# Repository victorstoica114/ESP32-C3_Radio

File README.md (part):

# ESP32-C3 Radio

PlatformIO project for testing multiple radio modules with an ESP32-C3 board,
an optional SSD1306 OLED display, and serial/AT-command based firmware variants.

The project is organized as a single PlatformIO application. The active radio
module and firmware variant are selected from `src/main.cpp`, and the matching
source file is included by `src/module_selection.h`.

## Measured radio energy

The repository includes a measured comparison of TX and RX event energy across
28 radio-module and board variants for a common 32-byte application payload.
The logarithmic scale makes the full range visible, from NRF24L01 devices to
high-power E32 and LoRa implementations. Click the chart to open the complete
35-page comparative study.

## Repository layout

| Folder | Purpose |
| --- | --- |
| `src/` | ESP32 firmware |
| `PCB/` | KiCad boards and supply-voltage table |
| `measurements/raw/` | All local PPK captures and source metadata; excluded from Git |
| `power_profiler/radio_power_profiler/`, `power_profiler/tools/` | Acquisition UI and analysis tools |
| `power_profiler/comparisons/` | Reviewed results and comparison exports |
| `power_profiler/audits/` | Measurement checks and supporting evidence |
| `power_profiler/study/` | Comparative study, figures and editable sources |
| `test/`, `power_profiler/tests/` | Radio checks and software tests |

See [the measurement directory guide](measurements/README.md) for RAW and WIRE
locations. New captures use the same local directory regardless of the shell's
working directory.

See `CHANGELOG.md` for notable project changes.

## License

Project source code is released under the MIT License. See `LICENSE`.

Third-party libraries and vendor/manufacturer datasheets keep their own
licenses and redistribution terms. See `THIRD_PARTY_NOTICES.md`.

## Hardware target

- MCU: ESP32-C3 DevKitC-02
- Framework: Arduino
- Build system: PlatformIO
- Optional display: SSD1306 128x64 OLED via U8g2

See the [module supply-voltage list](PCB/TENSIUNI_ALIMENTARE.md) for the
3.3 V and 5 V inputs used by the different radio adapter boards.

Common pins used by many sketches:

- OLED SDA: GPIO 5
- OLED SCL: GPIO 6
- Status LED: GPIO 8
- SPI CS/NSS: GPIO 7

The integrated OLED on the ESP32-C3 OLED devboard is wired to GPIO 5/GPIO 6.
Module schematics may expose other SDA/SCL labels for external headers, but that
does not change the onboard OLED wiring. If a future board/module variant uses a
different OLED wiring, document that exception in the module section below.

Some radio modules share GPIO 5/GPIO 6 with SPI MISO/MOSI. In the affected
firmware variants, the OLED I2C bus is released after the splash screen and the
SPI bus is reinitialized before starting the radio.

## Dependencies

Defined in `platformio.ini`:

- `jgromes/RadioLib`
- `olikraus/U8g2`
- `xreef/LoRa_E32_Series_Library`
- Arduino ESP32 built-in libraries such as `SPI`, `Wire`, and `EEPROM`

## Selecting firmware

Edit `src/main.cpp`:

```cpp
#define RADIO_MODULE  RADIO_EBYTE_E79_CC1352P
#define RADIO_PROGRAM BRIDGE
```

Keep this include after the two defines:

```cpp
#include "module_selection.h"
```

## Supported modules

Use these values for `RADIO_MODULE` in the ESP32 PlatformIO firmware:

| RADIO_MODULE | Folder | Radio/module |
| --- | --- | --- |
| `RADIO_CC1101_V1_433` | `src/CC1101` | CC1101 V1, 433 MHz hardware/front-end |
| `RADIO_CC1101_V2_868` | `src/CC1101` | CC1101 V2, 868 MHz hardware/front-end |
| `RADIO_HC12` | `src/HC-12` | HC-12 UART radio |
| `RADIO_NRF24L01` | `src/NRF24L01` | nRF24L01/nRF24L01+ |
| `RADIO_RA01_SX1278` | `src/RA-01(SX1278)` | Ai-Thinker RA-01, SX1278 |
| `RADIO_RA01H_SX1276` | `src/RA-01H(SX1276)` | RA-01H, SX1276 |
| `RADIO_RA01SH_SX1262` | `src/RA-01SH(SX1262)` | RA-01SH, SX1262 |
| `RADIO_RA02_SX1278` | `src/RA-02(SX1278)` | RA-02, SX1278 |
| `RADIO_E28_SX1280` | `src/E28(SX1280)` | E28, SX1280 2.4 GHz |
| `RADIO_EBYTE` | `src/Ebyte` | Ebyte E32 UART LoRa module |
| `RADIO_EBYTE_E32_868T30D` | `src/Ebyte` | Ebyte E32 868T30D UART LoRa module |
| `RADIO_EBYTE_E32_433T33D` | `src/Ebyte` | Ebyte E32 433T33D UART LoRa module |
| `RADIO_EBYTE_E22_SX1268` | `src/Ebyte E22(SX1268)` | Ebyte E22 SPI LoRa module, SX1268 |
| `RADIO_EBYTE_E280_SX1280` | `src/Ebyte E280(SX1280)` | Ebyte E280-2G4T12S UART/TTL module, SX1280 |
| `RADIO_EBYTE_E79_CC1352P` | `src/Ebyte E79(CC1352P)` | Ebyte E79-400DM2005S, TI CC1352P wireless MCU |
| `RADIO_EBYTE_E07_400M10S` | `src/CC1101` | Ebyte E07-400M10S, CC1101, 410-450 MHz, 10 dBm nominal |
| `RADIO_EBYTE_E07_400MM10S` | `src/CC1101` | Ebyte E07-400MM10S, CC1101, 10 dBm nominal |
| `RADIO_EBYTE_E07_900MM10S` | `src/CC1101` | Ebyte E07-900MM10S, CC1101, 855-925 MHz, 10 dBm nominal |
| `RADIO_EBYTE_E07_433M20S` | `src/CC1101` | Ebyte E07-433M20S, CC1101 + PA/LNA, 425-450.5 MHz, 20 dBm nominal |
| `RADIO_XL1276_D01_SX1276` | `src/XL1276-D01 (SX1276)` | XL1276-D01, SX1276 |

Standalone module-side radio firmware:

| Firmware | Primary repository | Local reference | Radio/module | Status |
| --- | --- | --- | --- | --- |
| RA08 AT modem | [victorstoica114/RA-08_AT-Commands](https://github.com/victorstoica114/RA-08_AT-Commands) | `src/RA-08(ASR6601)` | Ai-Thinker RA-08, ASR6601 LPWAN SoC | Functional and tested with two modules |
| RA09 AT modem | [victorstoica114/RA-09_AT-Commands](https://github.com/victorstoica114/RA-09_AT-Commands) | `src/RA-09(STM32WLE5)` | Ai-Thinker RA-09, STM32WLE5CCU6 Sub-GHz wireless MCU | Functional and tested with two modules; 20/20 bidirectional frames |
| E79 AT modem | [victorstoica114/Ebyte-E79-CC1352P-_AT_Modem_Firmware](https://github.com/victorstoica114/Ebyte-E79-CC1352P-_AT_Modem_Firmware) | `src/Ebyte E79(CC1352P)/CC1352P_AT_Modem_Firmware` | Ebyte E79-400DM2005S, TI CC1352P wireless MCU | Firmware 0.3.0; seven RF profiles; 343/0 hardware tests |

## Radio module gallery

The photographs below show the carrier boards and physical module
implementations used by this project and its power-measurement campaigns.

<table>
  <tr>
    <td align="center"><br><strong>CC1101 V1</strong></td>
    <td align="center"><br><strong>CC1101 V2</strong></td>
    <td align="center"><br><strong>E07-400M10S</strong></td>
    <td align="center"><br><strong>E07-433M20S</strong></td>
  </tr>
  <tr>
    <td align="center"><br><strong>E07-900MM10S</strong></td>
    <td align="center"><br><strong>E22</strong></td>
    <td align="center"><br><strong>E28</strong></td>
    <td align="center"><br><strong>E280</strong></td>
  </tr>
  <tr>
    <td align="center"><br><strong>E32-433T20D</strong></td>
    <td align="center"><br><strong>E32-433T33D</strong></td>
    <td align="center"><br><strong>E32-868T20D</strong></td>
    <td align="center"><br><strong>E32-868T30D</strong></td>
  </tr>
  <tr>
    <td align="center"><br><strong>E79 ESP32 bridge</strong></td>
    <td align="center"><br><strong>E79 direct UART</strong></td>
    <td align="center"><br><strong>HC-12</strong></td>
    <td align="center"><br><strong>nRF24L01</strong></td>
  </tr>
  <tr>
    <td align="center"><br><strong>nRF24L01 PA/LNA</strong></td>
    <td align="center"><br><strong>RA-01H</strong></td>
    <td align="center"><br><strong>RA-01SH</strong></td>
    <td align="center"><br><strong>RA-02</strong></td>
  </tr>
  <tr>
    <td align="center"><br><strong>RA-02 capacitor variant</strong></td>
    <td align="center"><br><strong>RA-08</strong></td>
    <td align="center"><br><strong>RA-09</strong></td>
    <td align="center"><br><strong>XL1276-D01</strong></td>
  </tr>
  <tr>
    <td align="center"><br><strong>SX1278 naked</strong></td>
    <td align="center"><br><strong>SX1278 shielded</strong></td>
    <td align="center"><br><strong>SX1278 capacitor</strong></td>
    <td align="center"><br><strong>SX1278 level shifter</strong></td>
  </tr>
</table>

## Firmware variants

Use these values for `RADIO_PROGRAM`:

| RADIO_PROGRAM | Meaning |
| --- | --- |
| `AT_COMMANDS` | AT-command shell and, for most modules, transparent TX mode |
| `BIDIRECTIONAL_RX_TX` | Bidirectional RX/TX example |
| `RECEIVE` | Receive-only example |
| `SETTINGS` | Radio settings/configuration example |
| `TRANSMIT` | Transmit-only example |
| `BRIDGE` | UART/Serial bridge example |

Availability by module:

| Module | AT_COMMANDS | BIDIRECTIONAL_RX_TX | RECEIVE | SETTINGS | TRANSMIT | BRIDGE |
| --- | --- | --- | --- | --- | --- | --- |
| `RADIO_CC1101_V1_433` | yes | yes | yes | yes | yes | no |
| `RADIO_CC1101_V2_868` | yes | no | no | no | no | no |
| `RADIO_HC12` | yes | yes | no | no | no | no |
| `RADIO_NRF24L01` | yes | yes | no | no | no | no |
| `RADIO_RA01_SX1278` | yes | yes | no | yes | no | no |
| `RADIO_RA01H_SX1276` | yes | yes | no | no | no | no |
| `RADIO_RA01SH_SX1262` | yes | yes | no | yes | no | no |
| `RADIO_RA02_SX1278` | yes | yes | no | yes | no | no |
| `RADIO_E28_SX1280` | yes | yes | no | yes | no | no |
| `RADIO_EBYTE` | yes | no | no | no | no | yes |
| `RADIO_EBYTE_E32_868T30D` | yes | no | no | no | no | no |
| `RADIO_EBYTE_E32_433T33D` | yes | no | no | no | no | no |
| `RADIO_EBYTE_E22_SX1268` | yes | no | no | no | no | no |
| `RADIO_EBYTE_E280_SX1280` | yes | no | no | no | no | no |
| `RADIO_EBYTE_E79_CC1352P` | yes | no | no | no | no | yes |
| `RADIO_EBYTE_E07_400M10S` | yes | no | no | no | no | no |
| `RADIO_EBYTE_E07_400MM10S` | yes | no | no | no | no | no |
| `RADIO_EBYTE_E07_900MM10S` | yes | no | no | no | no | no |
| `RADIO_EBYTE_E07_433M20S` | yes | no | no | no | no | no |
| `RADIO_XL1276_D01_SX1276` | yes | no | yes | yes | yes | no |
| RA08 AT modem | yes | no | no | no | no | no |
| RA09 AT modem | yes | no | no | no | no | no |

If a module/program combination is not available, compilation stops with a clear
`#error` message from `src/module_selection.h`.

## External Module Firmware

Some modules are wireless MCUs rather than direct ESP32 radio peripherals. Their
module-side firmware is kept separately from the ESP32 PlatformIO firmware.

### Ai-Thinker RA-08

The RA-08 ASR6601 AT modem firmware lives in its own repository:
[victorstoica114/RA-08_AT-Commands](https://github.com/victorstoica114/RA-08_AT-Commands).
That project turns the RA-08 into a standalone UART AT radio modem. This
repository keeps only a small source reference under
`src/RA-08(ASR6601)` (`main.c`, `at_modem.c`, IRQ glue, and headers).
Build support, drivers, startup code, linker scripts, and the ARM GCC toolchain
belong in the separate RA-08 firmware repository.

The RA-08 modem was validated on two modules over USB serial at `115200` baud,
including AT command parsing, parameter validation, sleep/wake guardrails,
manual frequency mode, channel mode, and bidirectional packet exchange.

### Ai-Thinker RA-09

The RA-09 STM32WLE5CCU6 AT modem firmware lives in its own repository:
[victorstoica114/RA-09_AT-Commands](https://github.com/victorstoica114/RA-09_AT-Commands).
The application uses LPUART1 on PA2/PA3, exposed by the module as
`TX2`/`RX2`, and receives continuously after boot. Plain UART messages are
transmitted transparently, so `AT+SEND` is optional.

This repository keeps the modem application, LPUART1 setup, interrupt glue,
and RA-09 RF interface as a compact source reference under
`src/RA-09(STM32WLE5)`. The complete STM32 HAL, CMSIS, radio middleware,
startup code, linker script, CMake build, and flashing tools remain in the
dedicated firmware repository.

The validated image was programmed through the STM32 UART bootloader on two
carriers, one using CH340C and one using CH9340C. Both passed modem identity
and configuration checks, followed by 10 of 10 transparent-data frames in
each direction without corruption.

## Build

From the project root:

```sh
pio run
```

Upload:

```sh
pio run --target upload
```

Open serial monitor:

```sh
pio device monitor
```

The serial baud rate depends on the selected firmware. Many AT-command variants
use `9600`, while some bridge examples use `115200`.

## AT command reference

All AT-command firmware variants implement `AT` for a basic connectivity check
and `AT?`/`AT+HELP` for the firmware-local help text. Commands not implemented
by the selected module return `#ERROR`.

Error responses are intentionally easy to filter: they start with `#` and are
printed with a CRLF line ending. Generic failures return `#ERROR`; specific
runtime guardrails return messages such as `#ERROR: RADIO_SLEEPING (send
AT+WAKE)`, `#ERROR: BRIDGE_OFF (send AT+BRIDGE=ON)`, or `#ERROR:
RADIO_NOT_READY (set config and run AT+APPLY)`.

`AT+DEFAULT` is intentionally kept as the safety net command. It restores known
firmware defaults, saves them where EEPROM/module storage is used, and reapplies
the radio configuration so communication can be recovered after a bad setting.

`AT+RX=OFF` means standby/receive disabled. Low-power sleep is a separate state
entered with `AT+SLEEP` and left with `AT+WAKE` where supported.

For UART radio modules, changing the module baud also retunes the ESP32 hardware
UART connected to that module. The ESP32 USB CDC serial port exposed to the PC is
virtual and is not used as the radio-module baud reference.

### CC1101

The Ebyte E07-400M10S, E07-400MM10S, E07-900MM10S, and E07-433M20S variants
use the same CC1101 AT firmware. Select the exact module with `RADIO_MODULE` so
the splash, configuration printout, allowed RF range, and EEPROM namespace
match the hardware. The E07-400M10S selection defaults to `433.920 MHz` and
limits `AT+FREQ` to its `410-450 MHz` RF range. The E07-900MM10S selection
defaults to `915.000 MHz` and limits `AT+FREQ` to its `855-925 MHz` RF range.
The E07-433M20S selection defaults to `433.920 MHz` and limits `AT+FREQ` to
its `425-450.5 MHz` RF range. On the local carriers, `GD00` is connected to
ESP32-C3 `GPIO1`, `GD02` to `GPIO3`, and module power passes through the
current-measurement jumper.

The local E07-900MM10S pair was hardware-validated at `915.000 MHz` using GFSK,
a 64-bit preamble, one tolerated sync-word bit error, CRC, and `-30 dBm`.
Those values are the firmware defaults and passed 20/20 isolated packets in
both directions. The modules support up to `10 dBm`, but the closely spaced
bench setup showed packet loss at higher power, consistent with receiver
overload; use more separation or RF attenuation for high-power tests.

The local E07-400M10S pair was hardware-validated at `433.920 MHz` with the
same conservative GFSK packet profile and `-30 dBm` TX power. Plain bridge
messages, without `AT+SEND`, passed 20/20 packets in both directions.

The local E07-433M20S pair was hardware-validated at `433.920 MHz`, GFSK, a
64-bit preamble, CRC, and the conservative `-30 dBm` CC1101 drive setting.
Automatic PA/LNA direction control and plain bridge traffic passed 20/20
packets in both directions.

Use `RADIO_CC1101_V1_433` for the local V1 CC1101 boards. Its firmware default
is `433.920 MHz`, the tested stable center frequency for the local 433 MHz
pair. Use `RADIO_CC1101_V2_868` for the local V2 CC1101 boards; that selection
uses the same firmware source, but `AT+DEFAULT` restores `868.000 MHz` and it
uses a separate EEPROM namespace. CC1101 chips can tune across multiple sub-GHz
bands, but the RF matching network, antenna, and any external PA/LNA are
band-specific. In the local test set, the V2 pair on COM39/COM40 was unreliable
at 433.920 MHz but passed cleanly at 868/869 MHz.

The E07-400MM10S selection compiles but still awaits equivalent paired-radio
hardware validation.

`E07-433M20S` includes an external PA/LNA and is rated around 20 dBm at module
level. Its active-HIGH `TXEN` and `RXEN` inputs are connected to ESP32-C3
`GPIO21` and `GPIO20`; the firmware switches them automatically and prevents
overlap. `AT+PWR` still controls the CC1101 drive/PATABLE preset exposed by
RadioLib, not a separate PA gain setting.

| Command | Meaning |
| --- | --- |
| `AT`, `AT?`, `AT+HELP`, `AT+CFG?` | Connectivity, help, and full configuration/status printout |
| `AT+APPLY`, `AT+RESET`, `AT+DEFAULT` | Apply current config, reset/reapply, or restore safe defaults |
| `AT+DEBUG=ON\|OFF`, `AT+DEBUG?` | Control debug output |
| `AT+BRIDGE=ON\|OFF`, `AT+BRIDGE?` | Control transparent serial-to-radio bridge mode |
| `AT+RX=ON`, `AT+RX=OFF` | Start receive or stop receive into standby |
| `AT+SLEEP`, `AT+WAKE` | Enter low-power sleep or wake and restore RX state |
| `AT+RSSI?`, `AT+LQI?`, `AT+STATUS?`, `AT+RANDOM?` | Packet/link diagnostics and one RSSI-noise random byte |
| `AT+FREQ?`, `AT+FREQ=<MHz>` | Query/set carrier frequency |
| `AT+BR?`, `AT+BR=<kbps>`, `AT+BR1..11` | Query/set bit rate or use a preset |
| `AT+DEV?`, `AT+DEV=<kHz>` | Query/set frequency deviation |
| `AT+BW?`, `AT+BW=<kHz>`, `AT+BW1..16` | Query/set receive bandwidth or use a preset |
| `AT+PWR?`, `AT+PWR=<-30\|-20\|-15\|-10\|0\|5\|7\|10>`, `AT+PWR1..8` | Query/set CC1101 drive power or use a preset |
| `AT+PRE?`, `AT+PRE=<bits>` | Query/set preamble length |
| `AT+SYNC?`, `AT+SYNC=<hex>` | Query/set 2-byte sync word |
| `AT+SYNCERR?`, `AT+SYNCERR=0\|1` | Query/set allowed sync-word error bits |
| `AT+CRC?`, `AT+CRC=ON\|OFF` | Query/set CRC |
| `AT+MOD?`, `AT+MOD=2FSK\|GFSK\|OOK\|4FSK` | Query/set modulation |
| `AT+SHAPE?`, `AT+SHAPE=NONE\|0.5` | Query/set data shaping |
| `AT+ENC?`, `AT+ENC=NRZ\|MANCHESTER\|WHITENING` | Query/set encoding |
| `AT+PKT?`, `AT+PKT=VARIABLE,<1..64>`, `AT+PKT=FIXED,<1..64>` | Query/set packet length mode |
| `AT+ADDR?`, `AT+ADDR=OFF`, `AT+ADDR=<node>,<broadcasts>` | Query/set address filtering |
| `AT+PROMISC?`, `AT+PROMISC=ON\|OFF` | Query/set promiscuous mode |
| `AT+CS?`, `AT+CS=ON\|OFF` | Query/set carrier-sense requirement |
| `AT+SETRADIO=FREQ,BR,DEV,BW,PWR,PRE,SYNC,CRC` | One-shot legacy CC1101 setup |

### HC-12

| Command | Meaning |
| --- | --- |
| `AT`, `AT?`, `AT+HELP`, `AT+CFG?` | Connectivity, help, and current firmware config |
| `AT+APPLY`, `AT+RESET`, `AT+DEFAULT` | Apply current config, reset/reapply, or restore defaults |
| `AT+DEBUG`, `AT+DEBUG=ON\|OFF`, `AT+DEBUG?` | Toggle/query debug output |
| `AT+BRIDGE=ON\|OFF`, `AT+BRIDGE?` | Control transparent USB Serial to HC-12 bridge |
| `AT+BAUD?`, `AT+BAUD=<1200..115200>` | Query/set HC-12 UART baud |
| `AT+UART?`, `AT+UART=8N1\|8O1\|8E1` | Query/set UART serial format |
| `AT+CHAN?`, `AT+CHAN=<0..127>` | Query/set HC-12 channel |
| `AT+POWER?`, `AT+POWER=<1..8>` | Query/set TX power level |
| `AT+FU?`, `AT+FU=<1..4>` | Query/set FU mode |
| `AT+V`, `AT+VERSION?` | Query module firmware version |
| `AT+INFO?` | Read module-side status/configuration |
| `AT+RAW=<cmd>` | Send a raw HC-12 AT command |
| `AT+SLEEP`, `AT+WAKE` | Put module to sleep or wake it |

### nRF24L01

| Command | Meaning |
| --- | --- |
| `AT`, `AT?`, `AT+HELP`, `AT+CFG?` | Connectivity, help, and full configuration/status printout |
| `AT+APPLY`, `AT+RESET`, `AT+DEFAULT` | Apply current config, reinitialize, or restore safe defaults |
| `AT+DEBUG=ON\|OFF`, `AT+DEBUG?` | Control debug output |
| `AT+STATUS?` | Print local RF/status information |
| `AT+RX=ON`, `AT+RX=OFF` | Start RX or enter standby |
| `AT+SLEEP`, `AT+WAKE` | Enter power-down or wake and restore RX state |
| `AT+FREQ?`, `AT+FREQ=<MHz>` | Query/set RF frequency |
| `AT+CHAN?`, `AT+CHAN=<0..125>` | Query/set 2.4 GHz channel |
| `AT+RATE?`, `AT+RATE=250\|1000\|2000` | Query/set data rate in kbps |
| `AT+PWR?`, `AT+PWR=<dBm>` | Query/set TX power |
| `AT+ADDR?`, `AT+ADDR=<hex>` | Query/set shared TX/RX pipe 0 address |
| `AT+ADDRWIDTH?`, `AT+ADDRWIDTH=3\|4\|5` | Query/set address width |
| `AT+TXADDR?`, `AT+TXADDR=<hex>` | Query/set TX address |
| `AT+RXADDR<n>?`, `AT+RXADDR<n>=<hex>` | Query/set RX pipe address, pipe `0..5` |
| `AT+PIPE<n>?`, `AT+PIPE<n>=ON\|OFF`, `AT+PIPES?` | Query/set pipe enable state |
| `AT+CRC?`, `AT+CRC=ON\|OFF` | Query/set CRC |
| `AT+AUTOACK?`, `AT+AUTOACK=<hexmask>` | Query/set auto-ack mask |
| `AT+AUTOACK<n>?`, `AT+AUTOACK<n>=ON\|OFF` | Query/set auto-ack for pipe `0..5` |
| `AT+RETRIES?`, `AT+RETRIES=<delay>,<count>` | Query/set retry delay/count |
| `AT+LNA?`, `AT+LNA=ON\|OFF` | Query/set LNA gain |
| `AT+DYN?`, `AT+DYN=ON\|OFF` | Query/set dynamic payloads |
| `AT+ACKPAY?`, `AT+ACKPAY=ON\|OFF` | Query/set ACK payload feature |
| `AT+PLEN?`, `AT+PLEN=<1..32>` | Query/set fixed payload length |

For transparent text payloads, nRF24L01 defaults to `AT+DYN=ON` so each serial
line can be sent at its actual length. If `AT+DYN=OFF` is selected, payload
lines must have exactly the configured `AT+PLEN` length; otherwise the firmware
returns `#ERROR: FIXED_PAYLOAD_LENGTH_MISMATCH`.

For sustained bidirectional validation across channel, rate, and power, use
`test/Test-Nrf24SustainedLink.ps1`. It records offered/received unique frames
and transmitter serial errors in a CSV plus a complete session log. The local
COM41/COM42 campaign is documented in
`power_profiler/comparisons/nrf24l01/VALIDATION.md`; it exposed repeatable
high-power loss at 250 and 1000 kbps, so the nRF24L01 web quick check includes
maximum-power/minimum-rate cases in both directions. The external-PA/LNA pair
on COM43/COM44 is characterized separately under
`power_profiler/comparisons/nrf24l01_pa/VALIDATION.md`; it must not be merged
with the plain-module baseline.

### SX1276/SX1278 modules

Applies to `RADIO_RA01_SX1278`, `RADIO_RA02_SX1278`,
`RADIO_RA01H_SX1276`, and `RADIO_XL1276_D01_SX1276`.

| Command | Meaning |
| --- | --- |
| `AT`, `AT?`, `AT+HELP`, `AT+CFG?` | Connectivity, help, and current config/status |
| `AT+APPLY`, `AT+RESET`, `AT+DEFAULT` | Apply current config, hardware reset/reapply, or restore defaults |
| `AT+DEBUG`, `AT+DEBUG=ON\|OFF`, `AT+DEBUG?` | Toggle/query debug output |
| `AT+RX=ON`, `AT+RX=OFF` | Start RX or stop RX into standby |
| `AT+SLEEP`, `AT+WAKE` | Enter sleep or wake and restore RX state |
| `AT+RSSI?`, `AT+SNR?`, `AT+FERR?`, `AT+CAD?`, `AT+RANDOM?` | Packet diagnostics, channel activity detection, random byte |
| `AT+FREQ?`, `AT+FREQ=<MHz>` | Query/set frequency; SX1278: `137..175` or `395..525`, SX1276: those bands plus `862..1020` |
| `AT+BW?`, `AT+BW=<kHz>` | Query/set LoRa bandwidth: `7.8`, `10.4`, `15.6`, `20.8`, `31.25`, `41.7`, `62.5`, `125`, `250`, `500` |
| `AT+SF?`, `AT+SF=<value>` | Query/set spreading factor |
| `AT+CR?`, `AT+CR=<5..8>` | Query/set coding rate denominator |
| `AT+SYNC?`, `AT+SYNC=<hex>` | Query/set sync word |
| `AT+PWR?`, `AT+PWR=<-4..17\|20>` | Query/set TX power |
| `AT+CURR?`, `AT+CURR=<0\|45..240>` | Query/set current limit where supported |
| `AT+PREAMBLE?`, `AT+PREAMBLE=<6..65535>` | Query/set preamble length |
| `AT+GAIN?`, `AT+GAIN=<0..6>` | Query/set RX gain where supported |
| `AT+CRC?`, `AT+CRC=ON\|OFF` | Query/set CRC |
| `AT+HEADER?`, `AT+HEADER=EXPLICIT`, `AT+HEADER=IMPLICIT,<1..255>` | Query/set explicit or implicit header mode |
| `AT+IQ?`, `AT+IQ=ON\|OFF` | Query/set IQ inversion |
| `AT+FHSS?`, `AT+FHSS=<0..255>` | Query/set FHSS hopping period |
| `AT+SET=<FREQ>,<BW>,<SF>,<CR>,<SYNC>,<PWR>,<CURR>,<PRE>,<GAIN>,<CRC>` | Batch-set LoRa parameters; some SX127x variants use the shorter format without `CURR`/`GAIN` |

### SX1262 RA-01SH

| Command | Meaning |
| --- | --- |
| `AT`, `AT?`, `AT+HELP`, `AT+CFG?` | Connectivity, help, and current config/status |
| `AT+APPLY`, `AT+RESET`, `AT+DEFAULT` | Apply current config, hardware reset/reapply, or restore defaults |
| `AT+DEBUG`, `AT+DEBUG=ON\|OFF`, `AT+DEBUG?` | Toggle/query debug output |
| `AT+RX=ON`, `AT+RX=OFF` | Start RX or stop RX into standby |
| `AT+SLEEP`, `AT+WAKE` | Enter sleep or wake and restore RX state |
| `AT+RSSI?`, `AT+SNR?`, `AT+FERR?`, `AT+CAD?`, `AT+RANDOM?`, `AT+STATUS?` | Packet/status diagnostics |
| `AT+FREQ?`, `AT+FREQ=<803..930 MHz>` | Query/set the RA-01SH front-end frequency |
| `AT+BW?`, `AT+BW=<kHz>` | Query/set bandwidth: `7.8`, `10.4`, `15.6`, `20.8`, `31.25`, `41.7`, `62.5`, `125`, `250`, `500` |
| `AT+SF?`, `AT+SF=<value>` | Query/set spreading factor |
| `AT+CR?`, `AT+CR=<5..8>` | Query/set coding rate denominator |
| `AT+SYNC?`, `AT+SYNC=<hex>` | Query/set sync word |
| `AT+PWR?`, `AT+PWR=<-9..22>` | Query/set TX power |
| `AT+CURR?`, `AT+CURR=<0..140>` | Query/set current limit |
| `AT+PREAMBLE?`, `AT+PREAMBLE=<1..65535>` | Query/set preamble length |
| `AT+GAIN?`, `AT+GAIN=<0..6>` | Query/set RX gain |
| `AT+CRC?`, `AT+CRC=ON\|OFF` | Query/set CRC |
| `AT+TCXO?`, `AT+TCXO=<0\|1.6..3.3>` | Query/set TCXO voltage, `0` for XTAL |
| `AT+REG?`, `AT+REG=LDO\|DCDC` | Query/set regulator mode |
| `AT+DIO2?`, `AT+DIO2=ON\|OFF` | Query/set DIO2 RF switch control |
| `AT+RXBOOST?`, `AT+RXBOOST=ON\|OFF` | Query/set boosted RX gain mode |
| `AT+HEADER?`, `AT+HEADER=EXPLICIT`, `AT+HEADER=IMPLICIT,<1..255>` | Query/set header mode |
| `AT+IQ?`, `AT+IQ=ON\|OFF` | Query/set IQ inversion |
| `AT+LDRO?`, `AT+LDRO=ON\|OFF` | Force low-data-rate optimization (`ON`) or restore automatic selection (`OFF`) |
| `AT+SET=<FREQ>,<BW>,<SF>,<CR>,<SYNC>,<PWR>,<CURR>,<PRE>,<GAIN>,<CRC>` | Batch-set LoRa parameters |

### SX1268 Ebyte E22

This is the SPI E22 variant wired as `NSS=GPIO7`, `DIO1=GPIO1`,
`BUSY=GPIO3`, `RESET=GPIO10`, with SPI on `GPIO4/5/6`. The onboard OLED uses
the same devboard wiring as the SX1278 tests: `SDA=GPIO5`, `SCL=GPIO6`. Because
those pins are shared with SPI, the firmware initializes the radio, recovers the
OLED I2C bus, draws the OLED splash, releases I2C, then reinitializes SPI.

| Command | Meaning |
| --- | --- |
| `AT`, `AT?`, `AT+HELP`, `AT+CFG?` | Connectivity, help, and current config/status |
| `AT+APPLY`, `AT+RESET`, `AT+DEFAULT` | Apply current config, hardware reset/reapply, or restore defaults |
| `AT+DEBUG`, `AT+DEBUG=ON\|OFF`, `AT+DEBUG?` | Toggle/query debug output |
| `AT+RX=ON`, `AT+RX=OFF` | Start RX or stop RX into standby |
| `AT+SLEEP`, `AT+WAKE` | Enter sleep or wake and restore RX state |
| `AT+RSSI?`, `AT+SNR?`, `AT+FERR?`, `AT+CAD?`, `AT+RANDOM?`, `AT+STATUS?` | Packet/status diagnostics |
| `AT+FREQ?`, `AT+FREQ=<410..493 MHz>` | Query/set frequency |
| `AT+BW?`, `AT+BW=<kHz>` | Query/set bandwidth: `7.8`, `10.4`, `15.6`, `20.8`, `31.25`, `41.7`, `62.5`, `125`, `250`, `500` |
| `AT+SF?`, `AT+SF=<7..12>` | Query/set spreading factor |
| `AT+CR?`, `AT+CR=<5..8>` | Query/set coding rate denominator |
| `AT+SYNC?`, `AT+SYNC=<hex>` | Query/set sync word |
| `AT+PWR?`, `AT+PWR=<-9..18>` | Query/set SX1268 front-stage TX power; E22 manual maps `18` to about `30 dBm` module output |
| `AT+CURR?`, `AT+CURR=<0..140>` | Query/set current limit |
| `AT+PREAMBLE?`, `AT+PREAMBLE=<1..65535>` | Query/set preamble length |
| `AT+GAIN?`, `AT+GAIN=<0..6>` | Stored for command compatibility; no SX126x-style gain control is applied |
| `AT+CRC?`, `AT+CRC=ON\|OFF` | Query/set CRC |
| `AT+TCXO?`, `AT+TCXO=<0\|1.6..3.3>` | Query/set TCXO voltage, `0` for XTAL |
| `AT+REG?`, `AT+REG=LDO\|DCDC` | Query/set regulator mode |
| `AT+DIO2?`, `AT+DIO2=ON\|OFF` | Query/set DIO2 RF switch control |
| `AT+RXBOOST?`, `AT+RXBOOST=ON\|OFF` | Query/set boosted RX gain mode |
| `AT+HEADER?`, `AT+HEADER=EXPLICIT`, `AT+HEADER=IMPLICIT,<1..255>` | Query/set header mode |
| `AT+IQ?`, `AT+IQ=ON\|OFF` | Query/set IQ inversion |
| `AT+LDRO?`, `AT+LDRO=ON\|OFF` | Query/set forced low-data-rate optimization |
| `AT+SET=<FREQ>,<BW>,<SF>,<CR>,<SYNC>,<PWR>,<CURR>,<PRE>,<GAIN>,<CRC>` | Batch-set LoRa parameters |

### Ebyte E280 UART SX1280

This is the `E280-2G4T12S` UART/TTL module from the local manual. It is based
on SX1280 internally, but the ESP32 talks to the module through UART and Ebyte's
binary configuration protocol, not through SPI/RadioLib. Current pin assumptions:
`RX=GPIO20`, `TX=GPIO21`, `M0=GPIO10`, `M1=GPIO3`, `M2=GPIO2`, `AUX=GPIO1`.

| Command | Meaning |
| --- | --- |
| `AT`, `AT?`, `AT+HELP`, `AT+CFG?` | Connectivity, help, and current module config/status |
| `AT+APPLY`, `AT+APPLY=TEMP`, `AT+RESET`, `AT+DEFAULT` | Save/apply, temporary apply, reset, or restore factory-safe defaults |
| `AT+INFO?`, `AT+AUX?` | Read module version bytes or AUX pin state |
| `AT+DEBUG=ON\|OFF`, `AT+DEBUG?` | Control debug output |
| `AT+BRIDGE=ON\|OFF`, `AT+BRIDGE?` | Control transparent USB Serial to E280 UART bridge |
| `AT+MODE?`, `AT+MODE=TRANSMISSION\|RSSI\|RANGING\|CONFIGURATION\|LOW_POWER` | Query/set M2/M1/M0 runtime mode |
| `AT+SLEEP`, `AT+WAKE` | Enter low-power mode or restore the previous normal mode |
| `AT+WINDOW=LOCAL\|REMOTE` | Send Ebyte `E2 E2 E2` or `E3 E3 E3` configuration-window command |
| `AT+ADDR?`, `AT+ADDR=<0..65535\|0x0000..0xFFFF>` | Query/set 16-bit module address |
| `AT+ADDH?`, `AT+ADDH=<0..255>` | Query/set high address byte |
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
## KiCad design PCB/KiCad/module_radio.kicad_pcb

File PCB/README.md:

# PCB

This directory contains the KiCad files for the radio adapter boards used by
the ESP32-C3 Radio project.

## Contents

- `KiCad/module_radio.kicad_pro`, `KiCad/module_radio.kicad_sch`, and
  `module_radio.kicad_pcb`: the main KiCad project.
- `KiCad/*.kicad_sch`: schematic sheets for the individual radio modules.
- `KiCad/Gerbers/`: exported Gerber archives for the supported adapter boards.
  These archives are kept in Git because they are useful for quick
  manufacturing checks and sharing without opening KiCad.
- `KiCad/Pictures/`: board renders/images, shown below.
- `KiCad/Librarys/`: project symbols, footprints, and 3D models.

Local KiCad-generated files such as `fp-info-cache`, `*.kicad_prl`,
`untitled.kicad_sch`, and `desktop.ini` are ignored.

The [module supply-voltage list](TENSIUNI_ALIMENTARE.md) is a simple table
of the radio modules and their 3.3 V or 5 V supply voltages.

## Board Images

| Module | Image |
| --- | --- |
| RA-01' |  |
| Ai-Thinker-Ra-02 |  |
| CC1101 |  |
| E07_400M10S |  |
| E07_433M20S |  |
| E07_900MM10S |  |
| E22 (SX1262) |  |
| E280 |  |
| E32-433T20D |  |
| E32-433T33D |  |
| E79-400DM2005S |  |
| E79-400DM2005S_V2.0 |  |
| E28-2G4M12XX |  |
| HC-12 |  |
| NRF24L01 |  |
| nRF24L01-PA-LNA |  |
| RA-01 |  |
| RA-02 |  |
| RA-09 |  |
| RFM69HCW |  |
| SX127X |  |
| TI-CC1101 |  |
| XL1276-D01 |  |

## Assembled Test Hardware

| Module | Assembled board |
| --- | --- |
| Ebyte E07-400M10S |  |
| Ebyte E07-433M20S |  |
| Ebyte E07-900MM10S |  |
| Ebyte E79-400DM2005S |  |
| Ai-Thinker RA-09 |  |

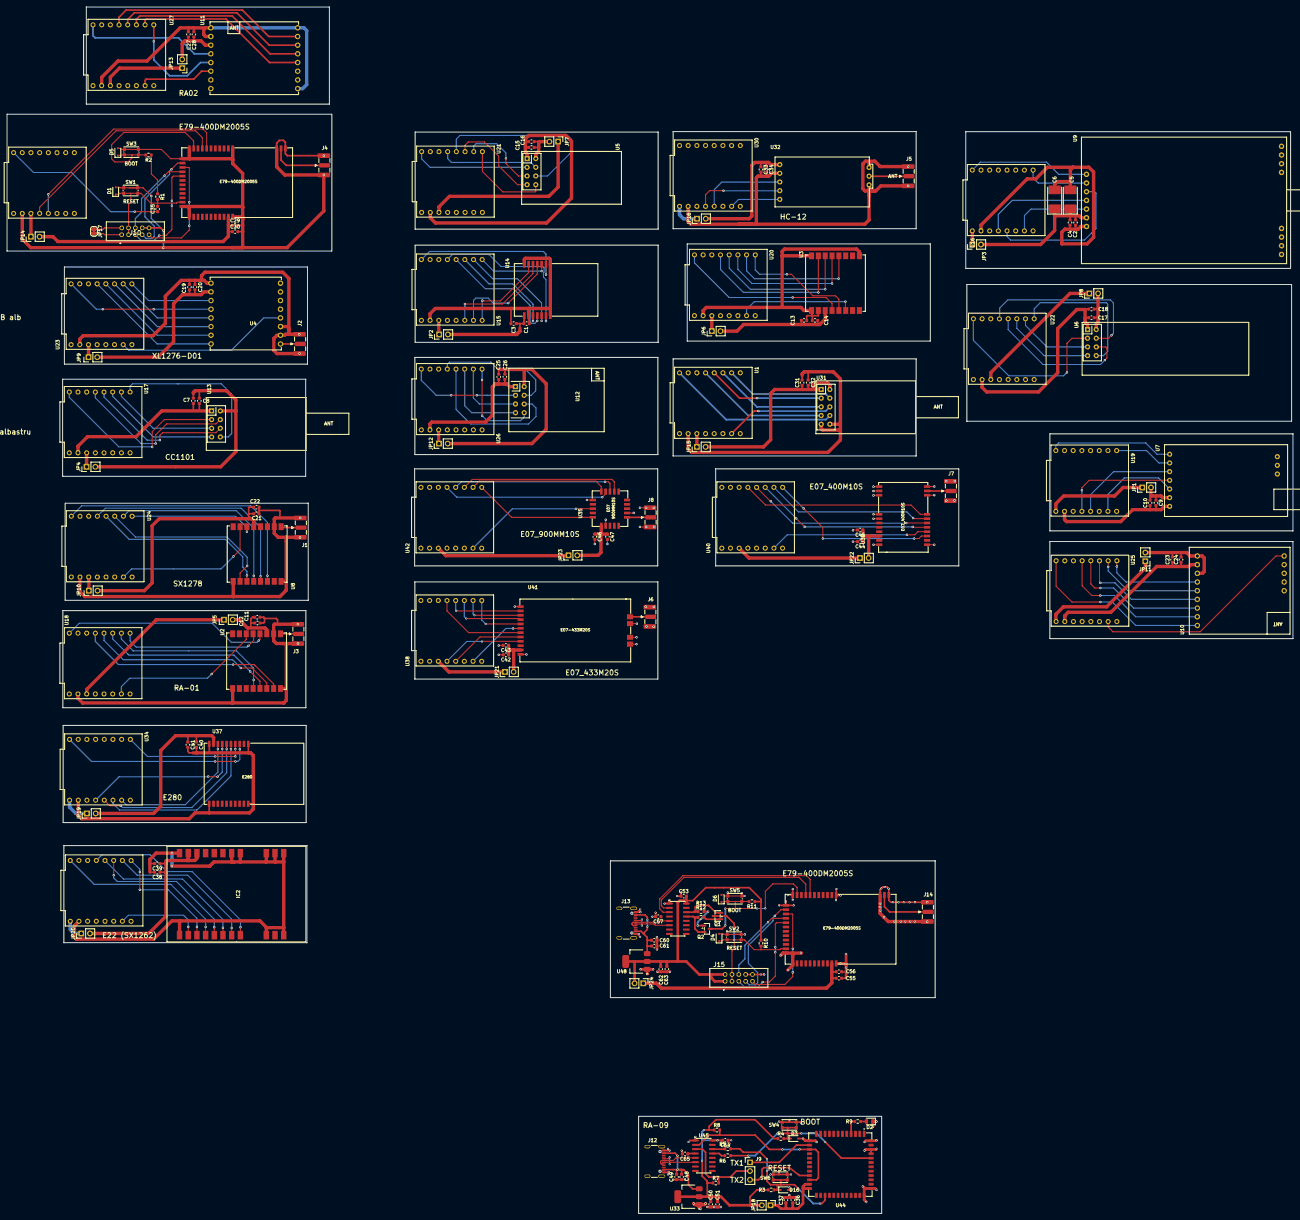
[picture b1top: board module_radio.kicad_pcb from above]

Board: 2 copper layers, 376.1 x 352.9 mm, 175 parts (0 on the bottom side), 244 nets.

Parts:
C1, C2, C7, C9, C11, C13, C15, C17, C19, C21, C23, C25, C27, C29, C31, C34, C35, C36, C38, C40, C42, C44, C46, C55: 100nF; C_0603_1608Metric
C3, C4, C8, C10, C12, C14, C16, C18, C20, C22, C24, C26, C28, C30, C32, C33, C39, C41, C43, C45, C47, C56: 1uF; C_0603_1608Metric
C5, C6: 47uF; CP_EIA-7132-28_AVX-C
C37, C49, C50, C60, C62: 10uF; C_0603_1608Metric
C48, C51, C53, C57, C61, C63, C64, C65: 0.1uF; C_0603_1608Metric
D1, D3, D4, D5, D6, D16: SP4020; D_SOD-323
D2: LED; D_0805_2012Metric
IC2: E22-400M30S; E22-900M30S-SX1262
J1, J2, J3, J4, J5, J6, J7, J8, J14: ANT; SMA_Samtec_SMA-J-P-H-ST-EM1_EdgeMount
J9: Conn_01x03_Pin; PinHeader_1x03_P2.54mm_Vertical
J10, J15: JTAG; AWHW210G0202TR
J12, J13: USB_C_Receptacle_USB2.0_14P; USB_C_Receptacle_GCT_USB4105-xx-A_16P_TopMnt_Horizontal
JP1, JP2, JP3, JP4, JP5, JP6, JP7, JP8, JP9, JP10, JP11, JP12, JP13, JP14, JP15, JP16, JP18, JP19, JP20, JP21, JP22, JP23, JP24: CUR; PinHeader_1x02_P2.54mm_Vertical
JP17: 3V3; SolderJumper-2_P1.3mm_Bridged_RoundedPad1.0x1.5mm
Q1, Q2: BC847; SOT-23
R1, R2, R3, R4, R9, R10, R11: 10k; R_0603_1608Metric
R5, R6: 0/NC; R_0603_1608Metric
R7, R8: 4k7; R_0603_1608Metric
R12, R13: 1k; R_0603_1608Metric_Pad0.98x0.95mm_HandSolder
SW1, SW2, SW6: RESET; SW_Push_1P1T_NO_CK_KMR2
SW3, SW4, SW5: BOOT; SW_Push_1P1T_NO_CK_KMR2
U1, U15, U16, U17, U18, U19, U20, U21, U22, U23, U24, U25, U26, U27, U28, U30, U34, U36, U38, U40, U42: ESP32-C3_OLED
U2: Ai-Thinker-Ra-01; Ai-Thinker-Ra-01-LoRa
U3: Ai-Thinker-Ra-02; Ai-Thinker-Ra-01-LoRa
U4: XL1276-D01
U5: NRF24L01; nRF24L01_Breakout
U6: nRF24L01+PA+LNA
U7: E32-433T20D; E32-xxxT20D
U8: SX127x
U9: E32-433T33D; E32-xxxT33D
U10: RFM69HCW
U11: RA-02
U12: RA-01
U13: CC1101
U14: E28-2G4M12XX; E28-2G4M12S
U29, U46: Ebyte_E79
U31: TI-CC1101
U32: HC-12
U33, U48: AMS1117-3.3; SOT-223-3_TabPin2
U35: Ebyte_E79; Ebyte_E07_900MM10S
U37: Ebyte_E280
U39: Ebyte_E79; Ebyte_E07_400M10S
U41: Ebyte_E79; Ebyte_E07_433M20S
U43: CH9340C; SOIC-16_3.9x9.9mm_P1.27mm
U44: RA-09
U45: CH340C; SOIC-16_3.9x9.9mm_P1.27mm

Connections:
+3.3V: R1.1, R2.1
/Ai-Thinker-Ra-01/+3V3: C11.1, C12.1, JP5.2 (B), U2.3 (VDD)
/Ai-Thinker-Ra-01/GND: C11.2, C12.2, J3.2 (Ext), U2.2 (GND), U2.9 (GND), U2.16 (GND), U18.2 (GND)
/Ai-Thinker-Ra-01/GPIO1/A1: U2.6 (DIO1), U18.7 (GPIO1/A1)
/Ai-Thinker-Ra-01/GPIO3/A3: U2.5 (DIO0), U18.9 (GPIO3/A3)
/Ai-Thinker-Ra-01/GPIO10: U2.4 (~RESET), U18.16 (GPIO10)
/Ai-Thinker-Ra-01/MISO: U2.13 (MISO), U18.11 (GPIO5/A5/MISO)
/Ai-Thinker-Ra-01/MOSI: U2.14 (MOSI), U18.12 (GPIO6/MOSI)
/Ai-Thinker-Ra-01/SCK: U2.12 (SCK), U18.10 (GPIO4/A4/SCK)
/Ai-Thinker-Ra-01/~SS: U2.15 (~NSS), U18.13 (GPIO7/SS)
/Ai-Thinker-Ra-02/+3V3: C13.1, C14.1, JP6.2 (B), U3.3 (VDD)
/Ai-Thinker-Ra-02/GND: C13.2, C14.2, U3.1 (GND), U3.2 (GND), U3.9 (GND), U3.16 (GND), U20.2 (GND)
/Ai-Thinker-Ra-02/GPIO1/A1: U3.6 (DIO1), U20.7 (GPIO1/A1)
/Ai-Thinker-Ra-02/GPIO3/A3: U3.5 (DIO0), U20.9 (GPIO3/A3)
/Ai-Thinker-Ra-02/GPIO10: U3.4 (~RESET), U20.16 (GPIO10)
/Ai-Thinker-Ra-02/MISO: U3.13 (MISO), U20.11 (GPIO5/A5/MISO)
/Ai-Thinker-Ra-02/MOSI: U3.14 (MOSI), U20.12 (GPIO6/MOSI)
/Ai-Thinker-Ra-02/SCK: U3.12 (SCK), U20.10 (GPIO4/A4/SCK)
/Ai-Thinker-Ra-02/~SS: U3.15 (~NSS), U20.13 (GPIO7/SS)
/Ai-Thinker-Ra-9/+3V3: C50.1, C51.1, C64.2, JP18.2 (B), R3.1, R4.1, R7.1, R8.1, U33.2 (VO), U45.16 (VCC)
/Ai-Thinker-Ra-9/+5V: C48.1, C49.1, J12.A4 (VBUS), J12.A9 (VBUS), J12.B4 (VBUS), J12.B9 (VBUS), U33.3 (VI)
/Ai-Thinker-Ra-9/BOOT: D3.1 (A1), R4.2, R6.2, SW4.2, U44.44 (PH3)
/Ai-Thinker-Ra-9/D+: J12.A6 (D+), J12.B6 (D+), U45.5 (UD+)
/Ai-Thinker-Ra-9/D-: J12.A7 (D-), J12.B7 (D-), U45.6 (UD-)
/Ai-Thinker-Ra-9/LED: R9.1, U44.4 (B8)
/Ai-Thinker-Ra-9/RX: J9.2, R7.2, U45.3 (RXD)
/Ai-Thinker-Ra-9/TX: R8.2, U44.15 (RX1), U44.22 (RX2), U45.2 (TXD)
/Ai-Thinker-Ra-9/TX1: J9.1, U44.14 (TX1)
/Ai-Thinker-Ra-9/TX2: J9.3, U44.21 (TX2)
/Ai-Thinker-Ra-9/~DTR: R6.1, U45.13 (~DTR)
/Ai-Thinker-Ra-9/~RST: D16.1 (A1), R3.2, R5.2, SW6.2, U44.27 (NRST)
/Ai-Thinker-Ra-9/~RTS: R5.1, U45.14 (~RTS)
/CC1101/+3V3: C7.1, C8.1, JP4.2 (B), U13.2 (VCC)
/CC1101/GND: C7.2, C8.2, U13.1 (GND), U17.2 (GND)
/CC1101/GPIO3/A3: U13.8 (GD02), U17.9 (GPIO3/A3)
/CC1101/GPIO10: U13.3 (GD00), U17.16 (GPIO10)
/CC1101/MISO: U13.7 (MISO), U17.11 (GPIO5/A5/MISO)
/CC1101/MOSI: U13.6 (MOSI), U17.12 (GPIO6/MOSI)
/CC1101/SCK: U13.5 (SCK), U17.10 (GPIO4/A4/SCK)
/CC1101/~SS: U13.4 (~CSN), U17.13 (GPIO7/SS)
/E22/+5V: C38.1, C39.1, IC2.9 (VCC), IC2.10 (VCC), JP20.2 (B)
/E22/GND: C38.2, C39.2, IC2.1 (GND), IC2.2 (GND), IC2.3 (GND), IC2.4 (GND), IC2.5 (GND), IC2.11 (GND), IC2.12 (GND), IC2.20 (GND), IC2.22 (GND), U36.2 (GND)
/E22/GPIO1/A1: IC2.13 (DIO1), U36.7 (GPIO1/A1)
/E22/GPIO3/A3: IC2.14 (BUSY), U36.9 (GPIO3/A3)
/E22/GPIO10: IC2.15 (~RST), U36.16 (GPIO10)
/E22/MISO: IC2.16 (MISO), U36.11 (GPIO5/A5/MISO)
/E22/MOSI: IC2.17 (MOSI), U36.12 (GPIO6/MOSI)
/E22/SCK: IC2.18 (SCK), U36.10 (GPIO4/A4/SCK)
/E22/~SS: IC2.19 (~SS), U36.13 (GPIO7/SS)
/E28-2G4M12XX/+3V3: C1.1, C3.1, JP2.2 (B), U14.1 (VCC)
/E28-2G4M12XX/GND: C1.2, C3.2, U14.2 (GND), U14.7 (GND), U14.8 (GND), U14.14 (GND), U15.2 (GND)
/E28-2G4M12XX/GPIO0/A0: U14.13 (DIO3), U15.8 (GPIO0/A0)
/E28-2G4M12XX/GPIO1/A1: U14.11 (DIO1), U15.7 (GPIO1/A1)
/E28-2G4M12XX/GPIO2/A2: U14.12 (DIO2), U15.6 (GPIO2/A2)
/E28-2G4M12XX/GPIO3/A3: U14.10 (BUSY), U15.9 (GPIO3/A3)
/E28-2G4M12XX/GPIO10: U14.9 (~RESET), U15.16 (GPIO10)
/E28-2G4M12XX/MISO: U14.3 (MISO/TX), U15.11 (GPIO5/A5/MISO)
/E28-2G4M12XX/MOSI: U14.4 (MOSI/RX), U15.12 (GPIO6/MOSI)
/E28-2G4M12XX/SCK: U14.5 (SCK/~RTS), U15.10 (GPIO4/A4/SCK)
/E28-2G4M12XX/~SS: U14.6 (~SS/CTS), U15.13 (GPIO7/SS)
/E32-433T20D/+5V: C9.1, C10.1, JP1.2 (B), U7.6 (VCC)
/E32-433T20D/GND: C9.2, C10.2, U7.7 (GND), U19.2 (GND)
/E32-433T20D/GPIO1/A1: U7.5 (AUX), U19.7 (GPIO1/A1)
/E32-433T20D/GPIO3/A3: U7.2 (M1), U19.9 (GPIO3/A3)
/E32-433T20D/GPIO10: U7.1 (M0), U19.16 (GPIO10)
/E32-433T20D/GPIO20/RX: U7.4 (TXD), U19.4 (GPIO20/RX)
/E32-433T20D/GPIO21/TX: U7.3 (RXD), U19.5 (GPIO21/TX)
/E32-433T33D/+5V: C2.1, C4.1, C5.1, C6.1, JP3.2 (B), U9.6 (VCC)
/E32-433T33D/GND: C2.2, C4.2, C5.2, C6.2, U9.7 (GND), U16.2 (GND)
/E32-433T33D/GPIO1/A1: U9.5 (AUX), U16.7 (GPIO1/A1)
/E32-433T33D/GPIO3/A3: U9.2 (M1), U16.9 (GPIO3/A3)
/E32-433T33D/GPIO10: U9.1 (M0), U16.16 (GPIO10)
/E32-433T33D/GPIO20/RX: U9.4 (TXD), U16.4 (GPIO20/RX)
/E32-433T33D/GPIO21/TX: U9.3 (RXD), U16.5 (GPIO21/TX)
/E280/+5V: C40.1, C41.1, JP19.2 (B), U37.9 (VCC)
/E280/GND: C40.2, C41.2, U34.2 (GND), U37.1 (GND), U37.10 (GND), U37.11 (GND), U37.20 (GND)
/E280/GPIO1/A1: U34.7 (GPIO1/A1), U37.8 (AUX)
/E280/GPIO2/A2: U34.6 (GPIO2/A2), U37.5 (M2)
/E280/GPIO3/A3: U34.9 (GPIO3/A3), U37.4 (M1)
/E280/GPIO10: U34.16 (GPIO10), U37.3 (M0)
/E280/GPIO20/RX: U34.4 (GPIO20/RX), U37.7 (TXD)
/E280/GPIO21/TX: U34.5 (GPIO21/TX), U37.6 (RXD)
/Ebyte_E07_400M10S/+3V3: C44.1, C45.1, JP22.2 (B), U39.9 (VCC)
/Ebyte_E07_400M10S/GND: C44.2, C45.2, J7.2 (Ext), U39.1 (GND), U39.2 (GND), U39.3 (GND), U39.4 (GND), U39.5 (GND), U39.11 (GND), U39.12 (GND), U39.20 (GND), U39.22 (GND), U40.2 (GND)
/Ebyte_E07_400M10S/GPIO1/A1: U39.15 (GD00), U40.7 (GPIO1/A1)
/Ebyte_E07_400M10S/GPIO3/A3: U39.14 (GD02), U40.9 (GPIO3/A3)
/Ebyte_E07_400M10S/MISO: U39.16 (MISO/GD01), U40.11 (GPIO5/A5/MISO)
/Ebyte_E07_400M10S/MOSI: U39.17 (MOSI), U40.12 (GPIO6/MOSI)
/Ebyte_E07_400M10S/SCK: U39.18 (SCK), U40.10 (GPIO4/A4/SCK)
/Ebyte_E07_400M10S/~SS: U39.19 (CSN), U40.13 (GPIO7/SS)
/Ebyte_E07_433M20S/+3V3: C42.1, C43.1, JP21.2 (B), U41.11 (VCC)
/Ebyte_E07_433M20S/GND: C42.2, C43.2, J6.2 (Ext), U38.2 (GND), U41.1 (GND), U41.12 (GND), U41.14 (GND), U41.15 (GND), U41.16 (GND)
/Ebyte_E07_433M20S/GPIO1/A1: U38.7 (GPIO1/A1), U41.6 (GD00)
/Ebyte_E07_433M20S/GPIO3/A3: U38.9 (GPIO3/A3), U41.5 (GD02)
/Ebyte_E07_433M20S/GPIO20/RX: U38.4 (GPIO20/RX), U41.9 (RXEN)
/Ebyte_E07_433M20S/GPIO21/TX: U38.5 (GPIO21/TX), U41.8 (TXEN)
/Ebyte_E07_433M20S/MISO: U38.11 (GPIO5/A5/MISO), U41.4 (MISO)
/Ebyte_E07_433M20S/MOSI: U38.12 (GPIO6/MOSI), U41.2 (MOSI)
/Ebyte_E07_433M20S/SCK: U38.10 (GPIO4/A4/SCK), U41.3 (SCK)
/Ebyte_E07_433M20S/~SS: U38.13 (GPIO7/SS), U41.7 (CSN)
/Ebyte_E07_900MM10S/+3V3: C46.1, C47.1, JP23.2 (B), U35.1 (VCC)
/Ebyte_E07_900MM10S/GND: C46.2, C47.2, J8.2 (Ext), U35.2 (GND), U35.7 (GND), U35.16 (GND), U42.2 (GND)
/Ebyte_E07_900MM10S/GPIO1/A1: U35.18 (GD00), U42.7 (GPIO1/A1)
/Ebyte_E07_900MM10S/GPIO3/A3: U35.20 (GD02), U42.9 (GPIO3/A3)
/Ebyte_E07_900MM10S/MISO: U35.12 (MISO/GD01), U42.11 (GPIO5/A5/MISO)
/Ebyte_E07_900MM10S/MOSI: U35.13 (MOSI), U42.12 (GPIO6/MOSI)
/Ebyte_E07_900MM10S/SCK: U35.15 (SCK), U42.10 (GPIO4/A4/SCK)
/Ebyte_E07_900MM10S/~SS: U35.14 (CSN), U42.13 (GPIO7/SS)
/Ebyte_E79/3V3: J10.2, JP17.1 (A)
/Ebyte_E79/+3V3: C29.1, C30.1, JP14.2 (B), U29.36 (VCC)
/Ebyte_E79/BOOT: D5.1 (A1), R2.2, SW3.2, U29.13 (DIO_15)
/Ebyte_E79/GPIO10: C35.1, U28.16 (GPIO10)
/Ebyte_E79/GPIO20/RX: U28.4 (GPIO20/RX), U29.11 (DIO_13)
/Ebyte_E79/GPIO21/TX: U28.5 (GPIO21/TX), U29.10 (DIO_12)
/Ebyte_E79/TCK: J10.9, U29.17 (JTAG_TCKC)
/Ebyte_E79/TDI: J10.5, U29.19 (DIO_17)
/Ebyte_E79/TDO: J10.6, U29.18 (DIO_16)
/Ebyte_E79/TMS: J10.7, U29.16 (JTAG_TMSC)
/Ebyte_E79/VREF: J10.1, JP17.2 (B)
/Ebyte_E79/~RST: C35.2, D1.1 (A1), J10.3, J10.4, R1.2, SW1.2, U29.25 (RESET_N)
/Ebyte_E80_CH9340C/+3V3: C53.2, C62.1, C63.1, J15.1, J15.2, JP24.2 (B), R10.1, R11.1, U43.16 (VCC), U48.2 (VO)
/Ebyte_E80_CH9340C/+5V: C60.1, C61.1, J13.A4 (VBUS), J13.A9 (VBUS), J13.B4 (VBUS), J13.B9 (VBUS), U48.3 (VI)
/Ebyte_E80_CH9340C/BOOT: D6.1 (A1), Q2.3 (C), R11.2, SW5.2, U46.13 (DIO_15)
/Ebyte_E80_CH9340C/D+: J13.A6 (D+), J13.B6 (D+), U43.5 (UD+)
/Ebyte_E80_CH9340C/D-: J13.A7 (D-), J13.B7 (D-), U43.6 (UD-)
/Ebyte_E80_CH9340C/RX: U43.3 (RXD), U46.10 (DIO_12)
/Ebyte_E80_CH9340C/TCK: J15.9, U46.17 (JTAG_TCKC)
/Ebyte_E80_CH9340C/TDI: J15.5, U46.19 (DIO_17)
/Ebyte_E80_CH9340C/TDO: J15.6, U46.18 (DIO_16)
/Ebyte_E80_CH9340C/TMS: J15.7, U46.16 (JTAG_TMSC)
/Ebyte_E80_CH9340C/TX: U43.2 (TXD), U46.11 (DIO_13)
/Ebyte_E80_CH9340C/~DTR: Q2.2 (E), R12.1, U43.13 (~DTR)
/Ebyte_E80_CH9340C/~RST: D4.1 (A1), J15.3, J15.4, Q1.3 (C), R10.2, SW2.2, U46.25 (RESET_N)
/Ebyte_E80_CH9340C/~RTS: Q1.2 (E), R13.1, U43.14 (~RTS)
/HC-12/+5V: C33.1, C34.1, JP16.2 (B), U32.1 (VCC)
/HC-12/GND: C33.2, C34.2, J5.2 (Ext), U30.2 (GND), U32.2 (GND), U32.7 (GND), U32.8 (GND)
/HC-12/GPIO1/A1: U30.7 (GPIO1/A1), U32.5 (SET)
/HC-12/GPIO20/RX: U30.4 (GPIO20/RX), U32.4 (TX)
/HC-12/GPIO21/TX: U30.5 (GPIO21/TX), U32.3 (RX)
/NRF24L01/+3V3: C15.1, C16.1, JP7.2 (B), U5.2 (VCC)
/NRF24L01/GND: C15.2, C16.2, U5.1 (GND), U21.2 (GND)
/NRF24L01/GPIO3/A3: U5.8 (IRQ), U21.9 (GPIO3/A3)
/NRF24L01/GPIO10: U5.3 (CE), U21.16 (GPIO10)
/NRF24L01/MISO: U5.7 (MISO), U21.11 (GPIO5/A5/MISO)
/NRF24L01/MOSI: U5.6 (MOSI), U21.12 (GPIO6/MOSI)
/NRF24L01/SCK: U5.5 (SCK), U21.10 (GPIO4/A4/SCK)
/NRF24L01/~SS: U5.4 (~CSN), U21.13 (GPIO7/SS)
/RA-01/+3V3: C25.1, C26.1, JP12.2 (B), U12.2 (VDD)
/RA-01/GND: C25.2, C26.2, U12.1 (GND), U26.2 (GND)
/RA-01/GPIO3/A3: U12.8 (DIO0), U26.9 (GPIO3/A3)
/RA-01/GPIO10: U12.3 (~RESET), U26.16 (GPIO10)
/RA-01/MISO: U12.7 (MISO), U26.11 (GPIO5/A5/MISO)
/RA-01/MOSI: U12.6 (MOSI), U26.12 (GPIO6/MOSI)
/RA-01/SCK: U12.5 (SCK), U26.10 (GPIO4/A4/SCK)
/RA-01/~SS: U12.4 (~NSS), U26.13 (GPIO7/SS)
/RA-02/+3V3: C27.1, C28.1, JP13.2 (B), U11.3 (VDD)
/RA-02/GND: C27.2, C28.2, U11.1 (GND), U11.2 (GND), U11.9 (GND), U11.16 (GND), U27.2 (GND)
/RA-02/GPIO1/A1: U11.6 (DIO1), U27.7 (GPIO1/A1)
/RA-02/GPIO3/A3: U11.5 (DIO0), U27.9 (GPIO3/A3)
/RA-02/GPIO10: U11.4 (~RESET), U27.16 (GPIO10)
/RA-02/MISO: U11.13 (MISO), U27.11 (GPIO5/A5/MISO)
/RA-02/MOSI: U11.14 (MOSI), U27.12 (GPIO6/MOSI)
/RA-02/SCK: U11.12 (SCK), U27.10 (GPIO4/A4/SCK)
/RA-02/~SS: U11.15 (~NSS), U27.13 (GPIO7/SS)
/RFM69HCW/+5V: C23.2, C24.2, JP11.2 (B), U10.6 (VDD), U10.8 (EN)
/RFM69HCW/GND: C23.1, C24.1, U10.7 (GND), U25.2 (GND)
/RFM69HCW/GPIO1/A1: U10.5 (DIO1), U25.7 (GPIO1/A1)
/RFM69HCW/GPIO3/A3: U10.9 (DIO0), U25.9 (GPIO3/A3)
/RFM69HCW/GPIO10: U10.14 (~RESET), U25.16 (GPIO10)
/RFM69HCW/MISO: U10.11 (MISO), U25.11 (GPIO5/A5/MISO)
/RFM69HCW/MOSI: U10.12 (MOSI), U25.12 (GPIO6/MOSI)
/RFM69HCW/SCK: U10.10 (SCK), U25.10 (GPIO4/A4/SCK)
/RFM69HCW/~SS: U10.13 (~NSS), U25.13 (GPIO7/SS)
/SX127x/+3V3: C21.1, C22.1, JP10.2 (B), U8.5 (VDD)
/SX127x/GND: C21.2, C22.2, J1.2 (Ext), U8.2 (GND), U8.9 (GND), U8.16 (GND), U24.2 (GND)
/SX127x/GPIO1/A1: U8.7 (DIO1), U24.7 (GPIO1/A1)
/SX127x/GPIO3/A3: U8.6 (DIO0), U24.9 (GPIO3/A3)
/SX127x/GPIO10: U8.14 (~RESET), U24.16 (GPIO10)
/SX127x/MISO: U8.10 (MISO), U24.11 (GPIO5/A5/MISO)
/SX127x/MOSI: U8.11 (MOSI), U24.12 (GPIO6/MOSI)
/SX127x/SCK: U8.12 (SCK), U24.10 (GPIO4/A4/SCK)
/SX127x/~SS: U8.13 (~NSS), U24.13 (GPIO7/SS)
/TI-CC1101/GND: C31.2, C32.2, U1.2 (GND), U31.9 (GND), U31.10 (GND)
/TI-CC1101/GPIO1/A1: U1.7 (GPIO1/A1), U31.6 (GD02)
/TI-CC1101/GPIO10: U1.16 (GPIO10), U31.8 (GD00)
/TI-CC1101/MISO: U1.11 (GPIO5/A5/MISO), U31.5 (MISO)
/TI-CC1101/MOSI: U1.12 (GPIO6/MOSI), U31.3 (MOSI)
/TI-CC1101/SCK: U1.10 (GPIO4/A4/SCK), U31.4 (SCK)
/TI-CC1101/~SS: U1.13 (GPIO7/SS), U31.7 (~CSN)
/XL1276-D01/+3V3: C19.1, C20.1, JP9.2 (B), U4.10 (VDD)
/XL1276-D01/GND: C19.2, C20.2, J2.2 (Ext), U4.2 (GND), U4.3 (GND), U4.9 (GND), U23.2 (GND)
/XL1276-D01/GPIO1/A1: U4.4 (DIO1), U23.7 (GPIO1/A1)
/XL1276-D01/GPIO3/A3: U4.11 (DIO0), U23.9 (GPIO3/A3)
/XL1276-D01/GPIO10: U4.12 (~RESET), U23.16 (GPIO10)
/XL1276-D01/MISO: U4.14 (MISO), U23.11 (GPIO5/A5/MISO)
/XL1276-D01/MOSI: U4.15 (MOSI), U23.12 (GPIO6/MOSI)
/XL1276-D01/SCK: U4.13 (SCK), U23.10 (GPIO4/A4/SCK)
/XL1276-D01/~SS: U4.16 (~NSS), U23.13 (GPIO7/SS)
/nRF24L01+PA+LNA/+3V3: C17.1, C18.1, JP8.2 (B), U6.2 (VCC)
/nRF24L01+PA+LNA/GND: C17.2, C18.2, U6.1 (GND), U22.2 (GND)
/nRF24L01+PA+LNA/GPIO3/A3: U6.8 (IRQ), U22.9 (GPIO3/A3)
/nRF24L01+PA+LNA/GPIO10: U6.3 (CE), U22.16 (GPIO10)
/nRF24L01+PA+LNA/MISO: U6.7 (MISO), U22.11 (GPIO5/A5/MISO)
/nRF24L01+PA+LNA/MOSI: U6.6 (MOSI), U22.12 (GPIO6/MOSI)
/nRF24L01+PA+LNA/SCK: U6.5 (SCK), U22.10 (GPIO4/A4/SCK)
/nRF24L01+PA+LNA/~SS: U6.4 (~CSN), U22.13 (GPIO7/SS)
GND: C29.2, C30.2, C36.2, C37.2, C48.2, C49.2, C50.2, C51.2, C53.1, C55.2, C56.2, C57.2, C60.2, C61.2, C62.2, C63.2, C64.1, C65.2, D1.2 (A2), D2.1 (K), D3.2 (A2), D4.2 (A2), D5.2 (A2), D6.2 (A2), D16.2 (A2), J4.2 (Ext), J10.8, J10.10, J12.A1 (GND), J12.A12 (GND), J12.B1 (GND), J12.B12 (GND), J13.A1 (GND), J13.A12 (GND), J13.B1 (GND), J13.B12 (GND), J14.2 (Ext), J15.8, J15.10, SW1.1, SW2.1, SW3.1, SW4.1, SW5.1, SW6.1, U28.2 (GND), U29.1 (GND), U29.3 (GND), U29.4 (GND), U29.14 (GND), U29.15 (GND), U29.26 (GND), U29.27 (GND), U29.37 (GND), U33.1 (GND), U43.1 (GND), U44.13 (GND), U44.36 (GND), U44.37 (GND), U44.45 (GND), U44.46 (GND), U44.48 (GND), U45.1 (GND), U46.1 (GND), U46.3 (GND), U46.4 (GND), U46.14 (GND), U46.15 (GND), U46.26 (GND), U46.27 (GND), U46.37 (GND), U48.1 (GND)
unnamed: D2.2 (A), R9.2
unnamed: J1.1 (In), U8.1 (ANT)
unnamed: J2.1 (In), U4.1 (ANT)
unnamed: J3.1 (In), U2.1 (ANT)
unnamed: J4.1 (In), U29.2 (ANT)
unnamed: J5.1 (In), U32.6 (ANT)
unnamed: J6.1 (In), U41.13 (ANT)
unnamed: J7.1 (In), U39.21 (ANT)
unnamed: J8.1 (In), U35.6 (ANT)
unnamed: J14.1 (In), U46.2 (ANT)
unnamed: JP1.1 (A), U19.1 (5V)
unnamed: JP2.1 (A), U15.3 (3V3)
unnamed: JP3.1 (A), U16.1 (5V)
unnamed: JP4.1 (A), U17.3 (3V3)
unnamed: JP5.1 (A), U18.3 (3V3)
unnamed: JP6.1 (A), U20.3 (3V3)
unnamed: JP7.1 (A), U21.3 (3V3)
unnamed: JP8.1 (A), U22.3 (3V3)
unnamed: JP9.1 (A), U23.3 (3V3)
unnamed: JP10.1 (A), U24.3 (3V3)
unnamed: JP11.1 (A), U25.1 (5V)
unnamed: JP12.1 (A), U26.3 (3V3)
unnamed: JP13.1 (A), U27.3 (3V3)
unnamed: JP14.1 (A), U28.3 (3V3)
unnamed: JP15.1 (A), U1.3 (3V3)
unnamed: JP16.1 (A), U30.1 (5V)
unnamed: JP19.1 (A), U34.1 (5V)
unnamed: JP20.1 (A), U36.1 (5V)
unnamed: JP21.1 (A), U38.3 (3V3)
unnamed: JP22.1 (A), U40.3 (3V3)
unnamed: JP23.1 (A), U42.3 (3V3)
unnamed: C55.1, C56.1, JP24.1 (A), U46.36 (VCC)
unnamed: Q1.1 (B), R12.2
unnamed: Q2.1 (B), R13.2
unnamed: C57.1, U43.4 (V3)
unnamed: C65.1, U45.4 (V3)
VCC: C31.1, C32.1, C36.1, C37.1, JP15.2 (B), JP18.1 (A), U31.1 (V+), U31.2 (VCC), U44.23 (VCC), U44.24 (VCC)

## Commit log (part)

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2026-06-27 Initial ESP32-C3 Radio project
2026-06-30 Add radio sleep commands and changelog
2026-06-30 Expand radio AT safeguards and docs
2026-06-30 Fix nRF24L01 payload handling
2026-06-30 Add Ebyte E22 SX1268 support
2026-06-30 Add Ebyte E280 SX1280 support
2026-06-30 Add E79 skeleton and planned RA modules
2026-06-30 Add RA08 AT modem source
2026-06-30 Document RA08 firmware repository
2026-06-30 Add MIT license and third-party notices
2026-06-30 Add E79 ESP32 bridge selection
2026-06-30 Add E07 selections and remove tracked datasheets
